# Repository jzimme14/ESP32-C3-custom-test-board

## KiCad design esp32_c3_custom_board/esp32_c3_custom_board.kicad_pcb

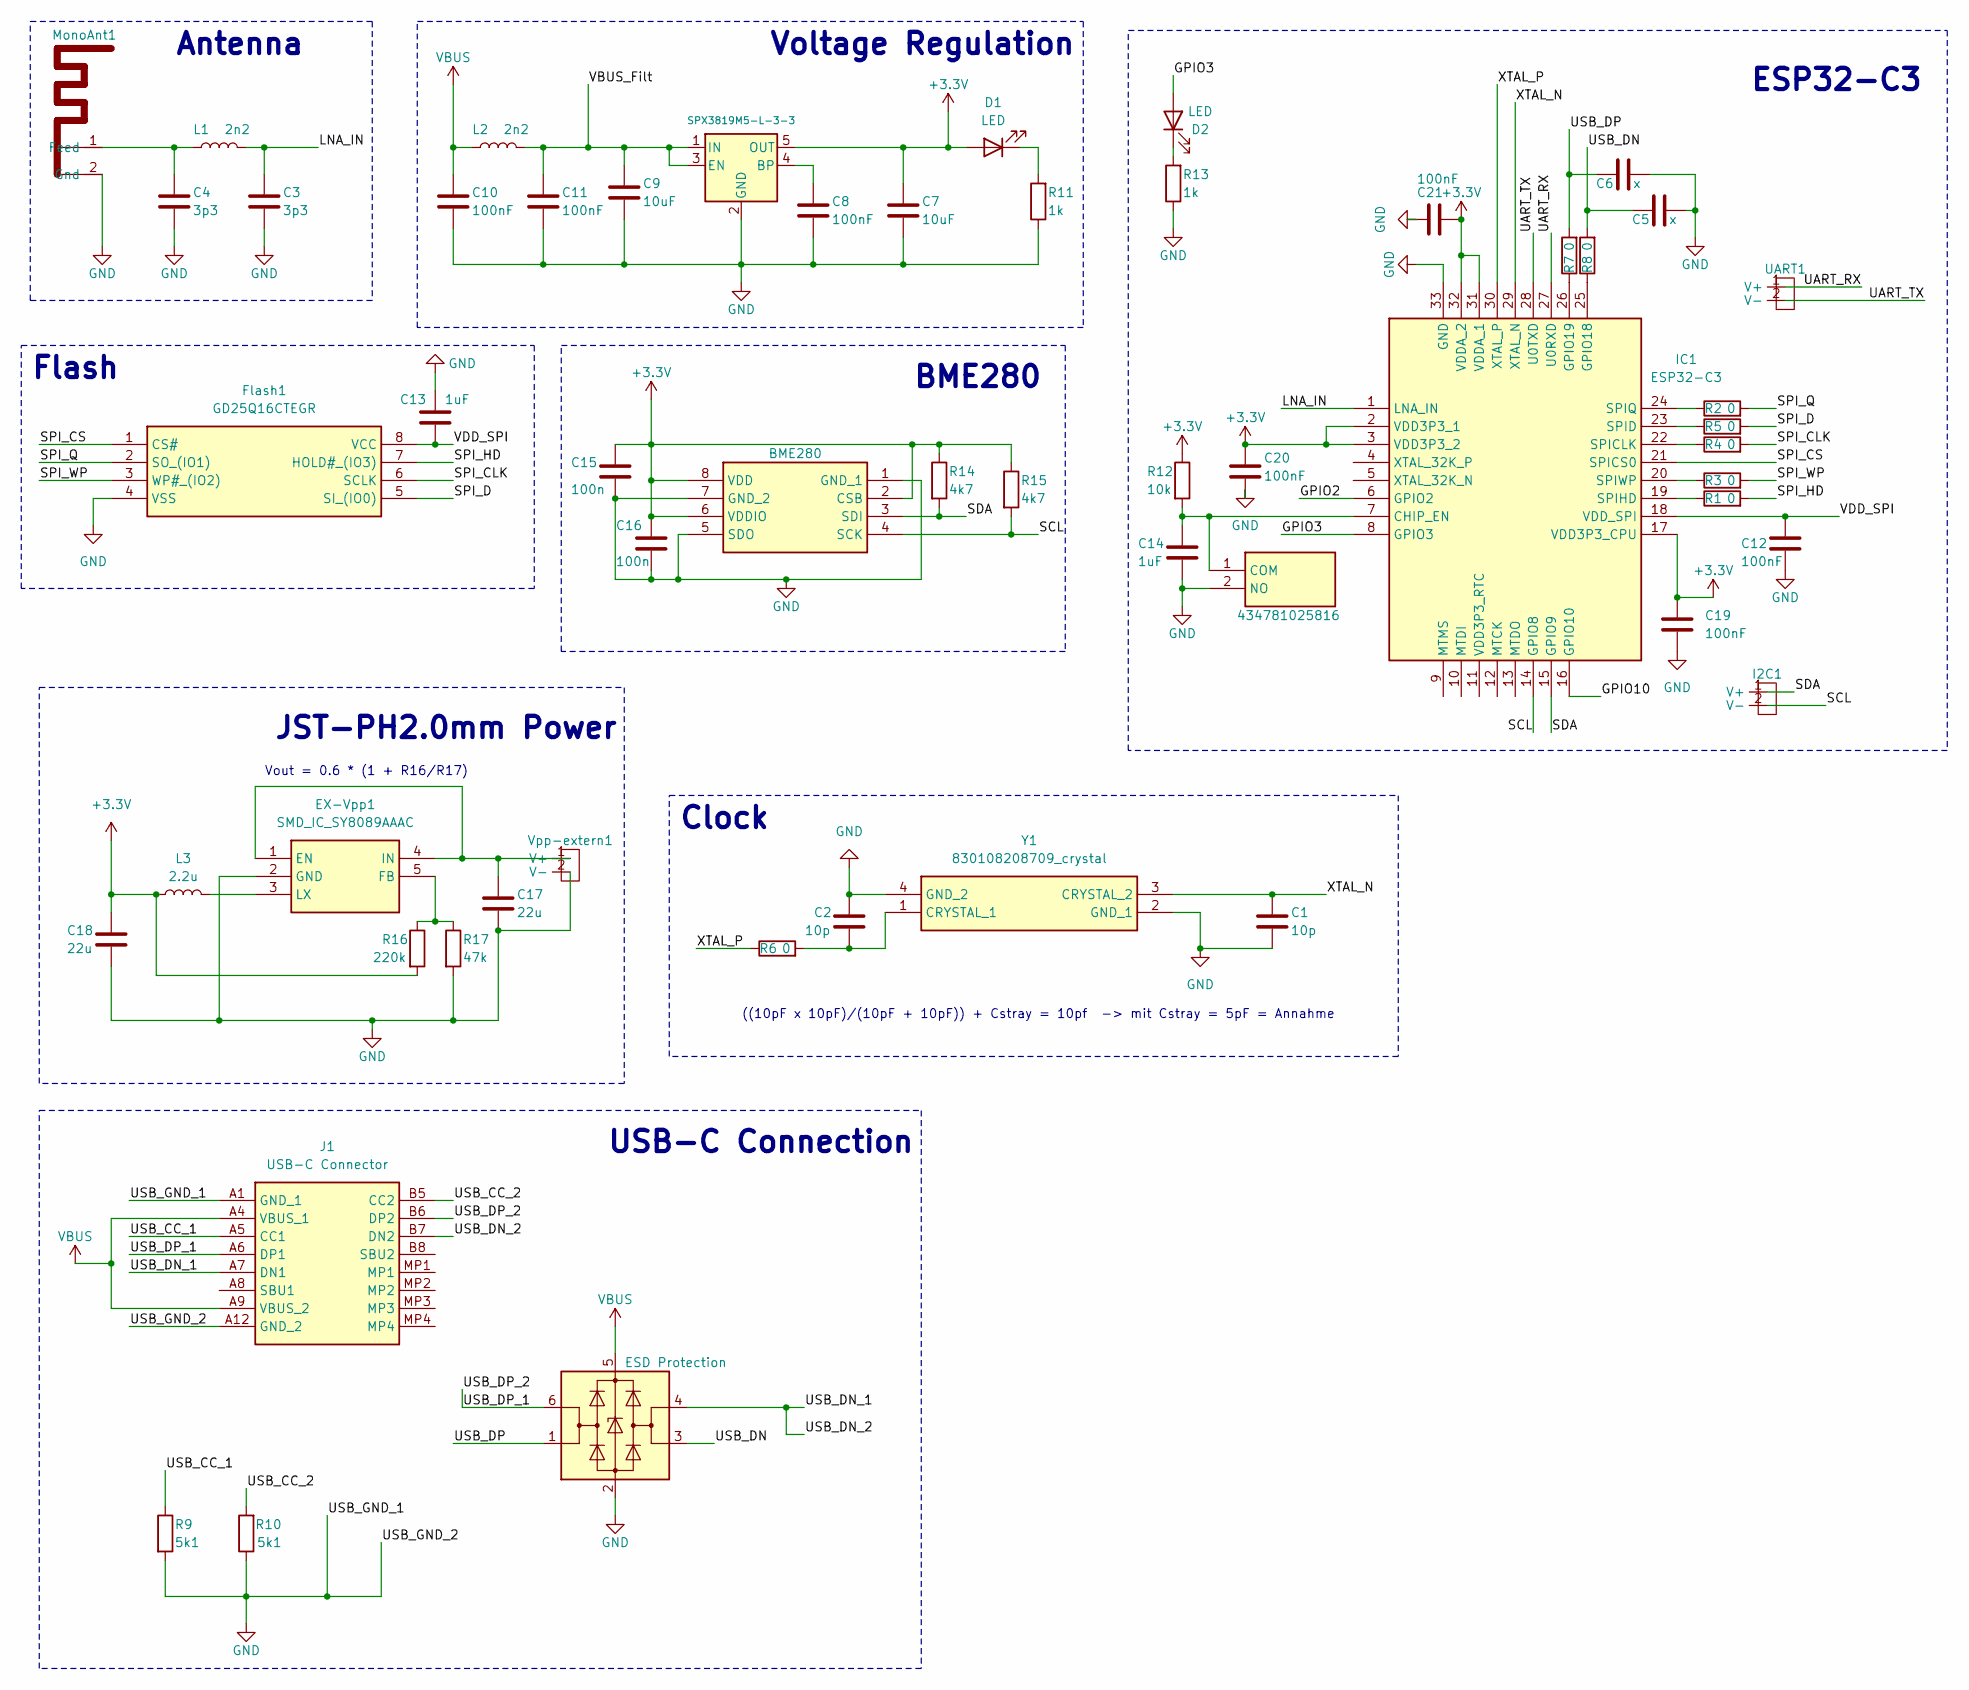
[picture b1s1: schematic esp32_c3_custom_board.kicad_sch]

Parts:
C1, C2: 10p; C_0402_1005Metric_Pad0.74x0.62mm_HandSolder
C3, C4: 3p3; C_0603_1608Metric_Pad1.08x0.95mm_HandSolder
C5, C6: x; C_0402_1005Metric_Pad0.74x0.62mm_HandSolder
C7, C9: 10uF; C_0603_1608Metric_Pad1.08x0.95mm_HandSolder
C8, C10, C11, C12, C19, C20, C21: 100nF; C_0603_1608Metric_Pad1.08x0.95mm_HandSolder
C13: 1uF; C_0402_1005Metric_Pad0.74x0.62mm_HandSolder
C14: 1uF; C_0603_1608Metric_Pad1.08x0.95mm_HandSolder
C15, C16: 100n; C_0402_1005Metric_Pad0.74x0.62mm_HandSolder
C17, C18: 22u; C_0805_2012Metric_Pad1.18x1.45mm_HandSolder
D1, D2: LED; ASCKCF00AP5R5010402
ESD1: ESD Protection; SOT95P280X145-6N
EX-Vpp1: SMD_IC_SY8089AAAC; SOT95P285X140-5N; Mouser Part Number 909-SMDICSY8089AAAC
Flash1: GD25Q16CTEGR; SOIC127P600X175-8N; Mouser Part Number 363-GD25Q16CTEGR
HM1: BME280; Mouser Part Number 262-BME280
I2C1: JST-PH2.0mm
IC1: ESP32-C3; QFN50P500X500X90-33N-D; Mouser Part Number 356-ESP32-C3
J1: USB-C Connector; GSB1C41110SSHR; Manufacturer_Part_Number GSB1C41110SSHR
L1, L2: 2n2; L_0603_1608Metric_Pad1.05x0.95mm_HandSolder
L3: 2.2u; L_0603_1608Metric_Pad1.05x0.95mm_HandSolder
MonoAnt1: Texas_SWRA117D_2.4GHz_Right
R1, R2, R3, R4, R5, R6, R7, R8: 0; R_0402_1005Metric_Pad0.72x0.64mm_HandSolder
R9, R10: 5k1; R_0402_1005Metric_Pad0.72x0.64mm_HandSolder
R11, R13: 1k; R_0603_1608Metric_Pad0.98x0.95mm_HandSolder
R12: 10k; R_0603_1608Metric_Pad0.98x0.95mm_HandSolder
R14, R15: 4k7; R_0402_1005Metric_Pad0.72x0.64mm_HandSolder
R16: 220k; R_0603_1608Metric_Pad0.98x0.95mm_HandSolder
R17: 47k; R_0603_1608Metric_Pad0.98x0.95mm_HandSolder
S1: 434781025816; Mouser Part Number 710-434781025816
UART1: JST-PH2.0mm
USB-Vpp1: SPX3819M5-L-3-3; SOT95P280X145-5N
Vpp-extern1: JST-PH2.0mm
Y1: 830108208709_crystal; 830108208709; Mouser Part Number 710-830108208709

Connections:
+3.3V: C7.1, C15.1, C16.1, C18.1, C19.1, C20.1, C21.1, D1.2 (A), HM1.2 (CSB), HM1.6 (VDDIO), HM1.8 (VDD), IC1.2 (VDD3P3_1), IC1.3 (VDD3P3_2), IC1.17 (VDD3P3_CPU), IC1.31 (VDDA_1), IC1.32 (VDDA_2), L3.1, R12.1, R14.1, R15.1, R16.2, USB-Vpp1.5 (OUT)
/GPIO2: IC1.6 (GPIO2)
/GPIO3: D2.2 (A), IC1.8 (GPIO3)
/GPIO10: IC1.16 (GPIO10)
/LNA_IN: C3.1, IC1.1 (LNA_IN), L1.2
/SCL: HM1.4 (SCK), I2C1.2 (V-), IC1.14 (GPIO8), R15.2
/SDA: HM1.3 (SDI), I2C1.1 (V+), IC1.15 (GPIO9), R14.2
/SPI_CLK: Flash1.6 (SCLK), R4.2
/SPI_CS: Flash1.1 (CS#), IC1.21 (SPICS0)
/SPI_D: Flash1.5 (SI_(IO0)), R5.2
/SPI_HD: Flash1.7 (HOLD#_(IO3)), R1.2
/SPI_Q: Flash1.2 (SO_(IO1)), R2.2
/SPI_WP: Flash1.3 (WP#_(IO2)), R3.2
/UART_RX: IC1.27 (U0RXD), UART1.1 (V+)
/UART_TX: IC1.28 (U0TXD), UART1.2 (V-)
/USB_CC_1: J1.A5 (CC1), R9.1
/USB_CC_2: J1.B5 (CC2), R10.2
/USB_DN: C5.1, ESD1.3 (I/O2), R8.2
/USB_DN_1: ESD1.4 (I/O2), J1.A7 (DN1), J1.B7 (DN2)
/USB_DP: C6.1, ESD1.1 (I/O1), R7.2
/USB_DP_1: ESD1.6 (I/O1), J1.A6 (DP1), J1.B6 (DP2)
/VBUS_Filt: C9.1, C11.1, L2.2, USB-Vpp1.1 (IN), USB-Vpp1.3 (EN)
/VDD_SPI: C12.1, C13.2, Flash1.8 (VCC), IC1.18 (VDD_SPI)
/XTAL_N: C1.1, IC1.29 (XTAL_N), Y1.3 (CRYSTAL_2)
/XTAL_P: IC1.30 (XTAL_P), R6.1
GND: C1.2, C2.1, C3.2, C4.2, C5.2, C6.2, C7.2, C8.2, C9.2, C10.2, C11.2, C12.2, C13.1, C14.2, C15.2, C16.2, C17.2, C18.2, C19.2, C20.2, C21.2, ESD1.2 (GND), EX-Vpp1.2 (GND), Flash1.4 (VSS), HM1.1 (GND_1), HM1.5 (SDO), HM1.7 (GND_2), IC1.33 (GND), J1.A1 (GND_1), J1.A12 (GND_2), MonoAnt1.2 (Gnd), R9.2, R10.1, R11.1, R13.1, R17.2, S1.2 (NO), USB-Vpp1.2 (GND), Vpp-extern1.2 (V-), Y1.2 (GND_1), Y1.4 (GND_2); also elsewhere on the board
unnamed: D1.1 (K), R11.2
unnamed: D2.1 (K), R13.2
unnamed 28: C17.1, EX-Vpp1.1 (EN), EX-Vpp1.4 (IN), Vpp-extern1.1 (V+); also elsewhere on the board
unnamed: EX-Vpp1.5 (FB), R16.1, R17.1
unnamed: EX-Vpp1.3 (LX), L3.2
unnamed: C14.1, IC1.7 (CHIP_EN), R12.2, S1.1 (COM)
unnamed: IC1.25 (GPIO18), R8.1
unnamed: IC1.26 (GPIO19), R7.1
unnamed: IC1.22 (SPICLK), R4.1
unnamed: IC1.23 (SPID), R5.1
unnamed: IC1.19 (SPIHD), R1.1
unnamed: IC1.24 (SPIQ), R2.1
unnamed: IC1.20 (SPIWP), R3.1
unnamed: C4.1, L1.1, MonoAnt1.1 (Feed)
unnamed: C8.1, USB-Vpp1.4 (BP)
unnamed: C2.2, R6.2, Y1.1 (CRYSTAL_1)
VBUS: C10.1, ESD1.5 (VBUS), J1.A4 (VBUS_1), J1.A9 (VBUS_2), L2.1

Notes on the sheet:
Clock
USB-C Connection
JST-PH2.0mm Power
ESP32-C3
Voltage Regulation
((10pF x 10pF)/(10pF + 10pF)) + Cstray = 10pf -> mit Cstray = 5pF = Annahme
Flash
Antenna
Vout = 0.6 * (1 + R16/R17)
BME280

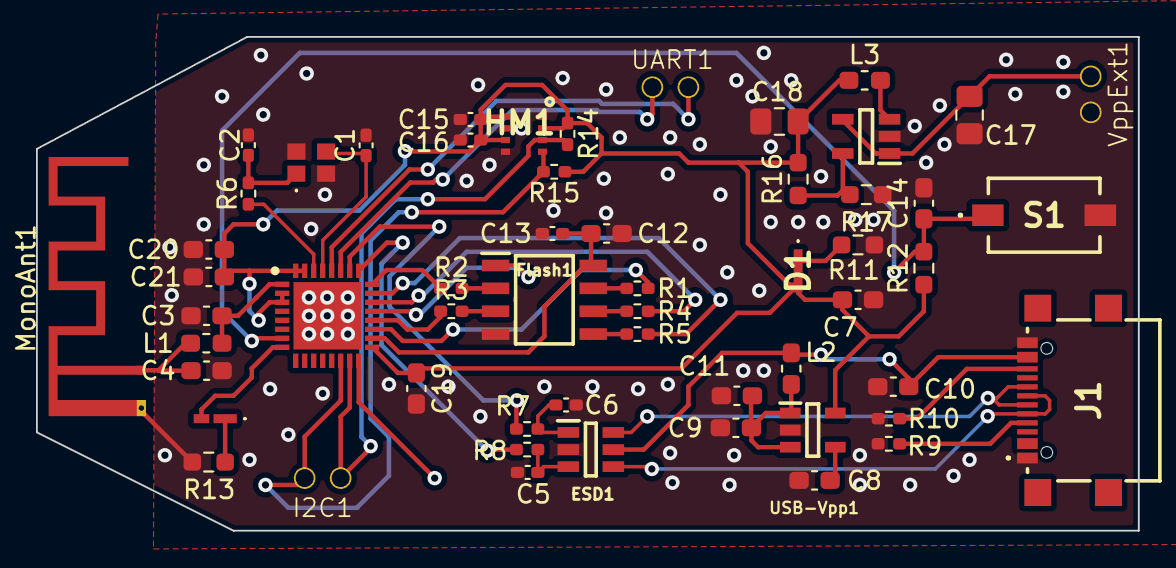
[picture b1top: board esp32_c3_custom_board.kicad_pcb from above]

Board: 2 copper layers, 61.2 x 27.4 mm, 56 parts (0 on the bottom side), 41 nets.

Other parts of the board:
VppExt1: JST-PH2.0mm

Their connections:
GND: VppExt1.2 (V-); also elsewhere on the board
unnamed 28: VppExt1.1 (V+); also elsewhere on the board

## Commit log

2024-05-03 init
2024-06-27 final design yallahhh
2024-06-27 gerber files generated
